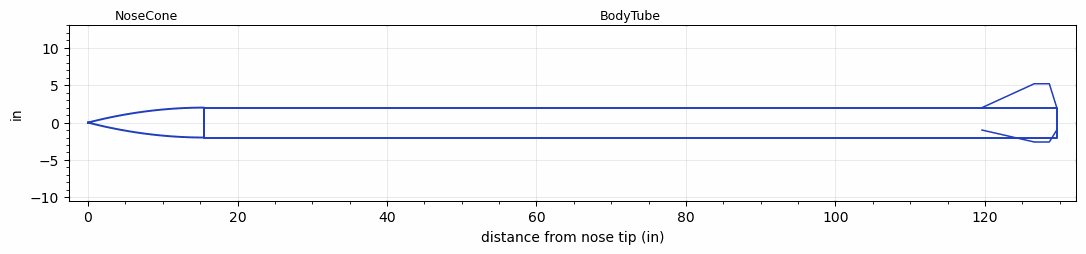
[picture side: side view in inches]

<RASAeroDocument>
 <FileVersion>2</FileVersion>
 <RocketDesign>
  <NoseCone>
   <Length>15.516</Length>
   <Diameter>4</Diameter>
   <Shape>Parabolic</Shape>
   <BluntRadius>0.1</BluntRadius>
   <Location>0</Location>
  </NoseCone>
  <BodyTube>
   <Length>114.1</Length>
   <Diameter>4</Diameter>
   <LaunchShoeArea>0.09</LaunchShoeArea>
   <Location>15.516</Location>
   <Fin>
    <Count>3</Count>
    <Chord>10</Chord>
    <Span>3.2</Span>
    <SweepDistance>7</SweepDistance>
    <TipChord>2</TipChord>
    <Thickness>0.25</Thickness>
    <LERadius>0.125</LERadius>
    <Location>10</Location>
    <AirfoilSection>Double Wedge</AirfoilSection>
    <FX1>1</FX1>
   </Fin>
  </BodyTube>
  <Surface>Rough Camouflage Paint</Surface>
  <ModifiedBarrowman>True</ModifiedBarrowman>
  <Turbulence>False</Turbulence>
  <UseBooster1>False</UseBooster1>
  <UseBooster2>False</UseBooster2>
 </RocketDesign>
 <LaunchSite>
  <Altitude>4596</Altitude>
  <Pressure>0</Pressure>
  <RodAngle>7</RodAngle>
  <RodLength>18</RodLength>
  <Temperature>100</Temperature>
  <WindSpeed>0</WindSpeed>
 </LaunchSite>
 <Recovery>
  <Altitude1>1000</Altitude1>
  <Altitude2>1500</Altitude2>
  <DeviceType1>Parachute</DeviceType1>
  <DeviceType2>Parachute</DeviceType2>
  <Event1>True</Event1>
  <Event2>True</Event2>
  <Size1>30.57</Size1>
  <Size2>96</Size2>
  <EventType1>Apogee</EventType1>
  <EventType2>Altitude</EventType2>
  <CD1>0.75</CD1>
  <CD2>2.2</CD2>
 </Recovery>
 <SimulationList>
  <Simulation>
   <SustainerEngine>N2900-CL  (CTI)</SustainerEngine>
   <SustainerLaunchWt>57.5</SustainerLaunchWt>
   <SustainerNozzleDiameter>2</SustainerNozzleDiameter>
   <SustainerCG>76.2</SustainerCG>
   <SustainerIgnitionDelay>0</SustainerIgnitionDelay>
   <Booster1SeparationDelay>0</Booster1SeparationDelay>
   <Booster1IgnitionDelay>0</Booster1IgnitionDelay>
   <IncludeBooster1>False</IncludeBooster1>
   <Booster2Delay>0</Booster2Delay>
   <IncludeBooster2>False</IncludeBooster2>
   <TimetoApogee>42.3389</TimetoApogee>
   <MaxAltitude>29224.58</MaxAltitude>
   <MaxVelocity>1585.222</MaxVelocity>
  </Simulation>
  <Simulation>
   <SustainerEngine>N2900-CL  (CTI)</SustainerEngine>
   <SustainerLaunchWt>67.8</SustainerLaunchWt>
   <SustainerNozzleDiameter>2</SustainerNozzleDiameter>
   <SustainerCG>74.2</SustainerCG>
   <SustainerIgnitionDelay>0</SustainerIgnitionDelay>
   <Booster1SeparationDelay>0</Booster1SeparationDelay>
   <Booster1IgnitionDelay>0</Booster1IgnitionDelay>
   <IncludeBooster1>False</IncludeBooster1>
   <Booster2Delay>0</Booster2Delay>
   <IncludeBooster2>False</IncludeBooster2>
   <TimetoApogee>44.54853</TimetoApogee>
   <MaxAltitude>34035.13</MaxAltitude>
   <MaxVelocity>1836.225</MaxVelocity>
  </Simulation>
  <Simulation>
   <SustainerEngine>N2900-CL  (CTI)</SustainerEngine>
   <SustainerLaunchWt>72.8</SustainerLaunchWt>
   <SustainerNozzleDiameter>2</SustainerNozzleDiameter>
   <SustainerCG>74.5</SustainerCG>
   <SustainerIgnitionDelay>0</SustainerIgnitionDelay>
   <Booster1SeparationDelay>0</Booster1SeparationDelay>
   <Booster1IgnitionDelay>0</Booster1IgnitionDelay>
   <IncludeBooster1>False</IncludeBooster1>
   <Booster2Delay>0</Booster2Delay>
   <IncludeBooster2>False</IncludeBooster2>
   <TimetoApogee>43.42872</TimetoApogee>
   <MaxAltitude>31439.54</MaxAltitude>
   <MaxVelocity>1698.255</MaxVelocity>
  </Simulation>
  <Simulation>
   <SustainerEngine>N3300  (AT)</SustainerEngine>
   <SustainerLaunchWt>58.1</SustainerLaunchWt>
   <SustainerNozzleDiameter>2</SustainerNozzleDiameter>
   <SustainerCG>72.8</SustainerCG>
   <SustainerIgnitionDelay>0</SustainerIgnitionDelay>
   <Booster1SeparationDelay>0</Booster1SeparationDelay>
   <Booster1IgnitionDelay>0</Booster1IgnitionDelay>
   <IncludeBooster1>False</IncludeBooster1>
   <Booster2Delay>0</Booster2Delay>
   <IncludeBooster2>False</IncludeBooster2>
   <TimetoApogee>38.42956</TimetoApogee>
   <MaxAltitude>25972.21</MaxAltitude>
   <MaxVelocity>1727.265</MaxVelocity>
  </Simulation>
  <Simulation>
   <SustainerEngine>N2900-CL  (CTI)</SustainerEngine>
   <SustainerLaunchWt>77.8</SustainerLaunchWt>
   <SustainerNozzleDiameter>2</SustainerNozzleDiameter>
   <SustainerCG>74.8</SustainerCG>
   <SustainerIgnitionDelay>0</SustainerIgnitionDelay>
   <Booster1SeparationDelay>0</Booster1SeparationDelay>
   <Booster1IgnitionDelay>0</Booster1IgnitionDelay>
   <IncludeBooster1>False</IncludeBooster1>
   <Booster2Delay>0</Booster2Delay>
   <IncludeBooster2>False</IncludeBooster2>
   <TimetoApogee>42.10894</TimetoApogee>
   <MaxAltitude>28966.67</MaxAltitude>
   <MaxVelocity>1577.022</MaxVelocity>
  </Simulation>
  <Simulation>
   <SustainerEngine>N2540-GR-P  (CTI)</SustainerEngine>
   <SustainerLaunchWt>75</SustainerLaunchWt>
   <SustainerCG>78.3</SustainerCG>
   <SustainerIgnitionDelay>0</SustainerIgnitionDelay>
   <Booster1SeparationDelay>0</Booster1SeparationDelay>
   <Booster1IgnitionDelay>0</Booster1IgnitionDelay>
   <IncludeBooster1>False</IncludeBooster1>
   <Booster2Delay>0</Booster2Delay>
   <IncludeBooster2>False</IncludeBooster2>
   <TimetoApogee>43.24875</TimetoApogee>
   <MaxAltitude>30148.62</MaxAltitude>
   <MaxVelocity>1659.882</MaxVelocity>
  </Simulation>
 </SimulationList>
</RASAeroDocument>
